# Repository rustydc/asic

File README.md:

# ASIC LLM research prototype

This repository contains the software-model starting point for a fixed-weight
LLM inference appliance built around the Qwen3.5 dense hybrid geometry.

* [`ARCHITECTURE.md`](ARCHITECTURE.md) records the current appliance and pipeline
  decisions, including the balanced FULL-retrieval policy for every global layer.
* [`fixed_llm_poc.py`](fixed_llm_poc.py) is the correctness-oriented PyTorch
  reference model. Its parameter names match the Hugging Face `Qwen3_5` text
  model so released checkpoints load with a prefix rename. It is not an
  optimized long-context training kernel.
* [`fabric/`](fabric/) defines the fixed-weight fabric tile: a via-programmed
  coefficient ROM feeding 64 MAC columns. It holds the bit-exact reference
  model, the coefficient compiler and via-pattern export, the model-to-tile
  mapping with area and latency estimates, synthesizable RTL verified
  against the model with Icarus Verilog, a yosys flow that measures the
  column datapath on open liberty files (sky130, IHP SG13G2, NanGate 45,
  ASAP7), an OpenSTA driver for pre-layout timing, and an OpenROAD
  place-and-route driver with its sky130 and ASAP7 results. `fabric/layer.py`
  and the vector-unit RTL beside the tile are the rest of the layer
  datapath: the norms, the causal convolution, the Gated DeltaNet state
  update and gates, SwiGLU, the residual adds, the rotary embedding and
  the attention core, as a bit-exact fixed-point model with the compiler
  for their constants, checked against the PyTorch reference and against
  the RTL in Icarus. `fabric/memory.py` and its RTL are the memory side:
  the per-context address map, the state DMA, the window and block
  append with the 4-bit index, the index scan and top-K, and the record
  reader into the attention core, with a float twin that reproduces the
  reference retrieval token by token. `fabric/hpi.py` and its RTL are the
  controller for the PSRAM board's chosen device, the AP Memory
  APS512XXN in x16 HPI mode, with a stripe unit over sixteen of them, the
  clock crossing to the core, and the PHY's delay lines with their DLL.
  `fabric/sequencer.py` and its RTL are the token sequencer: a layer's
  dataflow as a program of unit commands, proven against the integer
  layer, scheduled at full size, merged across tokens of different
  contexts so the memory port never waits, and run by a microcoded issue
  engine with per-buffer scoreboards. `fabric/engine.py` and
  `fabric/rtl/fabric_engine.sv` are the layer engine: that controller
  wired to the real tiles, vector units, state engines, attention cores
  and memory port through one vector buffer, running both layers'
  programs bit for bit against the integer model and the memory model,
  over the memory model or the HPI path itself, one token at a time or
  a prefill chunk of tokens on the multi-token tiles.
  `fabric/state.py` is the study that set the recurrent state's format,
  int8 with a per-head scale that carries the decay, halving the traffic
  the schedule showed to dominate; the global layer's traffic followed,
  with a head-major window read in page bursts, a page-per-request index
  scan and int4 keys and values.
* [`clash/`](clash/) contains a synthesizable four-stage ASIC-shard seed with a
  deliberately small fixed-coefficient datapath for early RTL and P&R work.
* [`sim/`](sim/) contains the cycle-stepped 32-stage appliance simulator for
  scheduling, phased global execution, backpressure, link, memory-bandwidth,
  and retrieval-geometry sweep experiments, with an energy model that turns
  the measured energy per MAC into board power at the simulated throughput.
* [`training/`](training/) contains the Qwen3.5 checkpoint importer, the
  retrieval candidates, and a layer-wise activation-distillation harness.
* [`hw/`](hw/) contains the block-level board descriptions of the host-attached
  1U: the 9B board (eight layer ASICs, two head-mode ASICs, sixteen LPDDR5X
  devices, one FPGA on a PCIe cable, a BMC, redundant CRPS supplies) and
  the 27B-class high-end variant (four sixteen-layer ASICs with HBM4 in
  the package, one head ASIC, liquid cooled), their consistency checks
  including a throughput-driven power budget, the rendered block diagrams,
  a derivation of the ASIC package and ball map from the power model and
  the interface list, a generator that turns either description into a
  KiCad 7 project with the board outline and chassis keep-outs, the ring
  placed as a regular polygon of rotated chips, stackup, all nets, and the
  activation ring routed, and a time-domain signal-integrity check of the
  PSRAM clock nets that settled on one clock per device.

## Reference geometries

| Preset | Source model | Hidden | Layers | Body params | Per-ASIC shard |
| --- | --- | ---: | ---: | ---: | ---: |
| `qwen3_5_9b` (default) | Qwen3.5-9B-Base | 4096 | 8 × (3 R + 1 G) | 6.9B | 866M |
| `qwen3_5_4b` | Qwen3.5-4B-Base | 2560 | 8 × (3 R + 1 G) | 3.6B | 447M |
| `qwen3_5_27b` | 27B-class stand-in (Qwen3.5-27B shapes) | 5120 | 16 × (3 R + 1 G) | 22.9B | 1.43B per group, two per die |

Both presets share the same recurrent heads (32 value × 16 key, 128-dim),
attention heads (16 query × 4 KV, 256-dim), and therefore the same per-context
state formats. Only the fabric width differs, so the 4B is a narrow build of the
same design. Select a preset with `ASICLMConfig.from_preset(name)`; every
variant in `training/variants.json` names one.

## Run

Run the tiny model smoke test and the geometry report in an environment with
PyTorch installed:

```bash
python fixed_llm_poc.py
python -m unittest discover -s training/tests -t .
python -m unittest discover -s sim/tests -t .
python -m unittest discover -s fabric/tests -t .   # RTL tests need iverilog; engine tests use verilator if present
python -m unittest discover -s hw/tests -t .
```

Import a released checkpoint (needs the `safetensors` package):

```bash
python -m training.qwen35_import --checkpoint /models/Qwen3.5-9B-Base \
    --output checkpoints/asic_init.pt
```

Simulate both geometries:

```bash
python -m sim.run --config sim/config/baseline.json     # 9B
python -m sim.run --config sim/config/qwen35_4b.json    # 4B
python -m sim.run --config sim/config/qwen35_9b_7nm_hbm.json   # 9B, 7 nm-class die, HBM
python -m sim.run --config sim/config/qwen35_9b_3nm_hbm.json   # 9B, 3 nm-class die, HBM
python -m sim.run --config sim/config/qwen35_27b_2nm_hbm.json  # 27B-class, 2 nm-class die, HBM4 (the high end)
```

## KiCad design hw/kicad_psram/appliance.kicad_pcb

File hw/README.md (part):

# Appliance board (revision A0)

Block-level schematic capture for the first appliance board. `board.yaml` is
the source of truth; `python -m hw.board` checks it and regenerates
`board.svg` (block diagram) and `board.md` (bill of materials, power, pin
budget, ring order). Two variants share the tools: `board_27b.yaml`, the
high-end 27B on HBM, and `board_psram.yaml`, the open-IP 9B on PSRAM
modules. Everything here is a budget to validate, not a vendor-
confirmed number, until the ASIC pinout and power are characterized.

```bash
python -m hw.board            # check, then write board.svg and board.md
python -m unittest discover -s hw/tests -t .
```

## Form factor: a host-attached 1U

The board is a single 420 × 360 mm board in a 1U rack chassis, attached to
a host over a PCIe cable. The first draft was a full-length PCIe card; the
energy model below moved it out of the slot. At 3 pJ per MAC the board
draws 0.5 to 1.6 kW of input across the throughput range, which is a rack
power supply and a row of fans, not a 600 W auxiliary connector on a
passively cooled card. The 1U also has the room the 50K tokens/s package
needs (29 mm bodies on a 230 mm ring) and a management controller. The
chassis layout:

* rear panel: the SlimSAS 8i host connector next to the FPGA, the BMC's
  RJ45, the optional SFP+ cage, the status LEDs;
* rear right: the PSU bay with two CRPS modules in a 1+1 redundant pair;
* the activation ring is a regular polygon in the left two thirds of the
  board, the FPGA at its rear vertex, the shared regulators and the clock
  generator in its middle;
* front: six 40 mm fans blowing front to back across the ring.

## Population

| Part | Qty | Role |
| --- | ---: | --- |
| Layer ASIC | 8 | four decoder layers each, personalized coefficient masks, layer-mode strap |
| Head ASIC | 2 | same die, head-mode strap, each holds half of the 248K-row LM head; no memory |
| LPDDR5X 16 Gb x32 | 16 | two per layer ASIC: 4 GB and 77 GB/s raw per ASIC at 9600 MT/s |
| Controller FPGA | 1 | PCIe Gen4 x8 endpoint over the host cable, ring source and sink, sampling, scheduling |
| DDR4 x16 | 4 | 4 GB on the FPGA for the embedding table and per-context metadata |
| Clock generator | 1 | reference clock to all eleven devices |
| BMC | 1 | AST2600-class: PSU PMBus, fan control, thermal, FPGA console, its own Ethernet |
| Host cable connector | 1 | SlimSAS 8i (SFF-8654): PCIe Gen4 x8 plus sideband to a host adapter card |
| CRPS receptacle | 2 | 12 V from each supply module, 1+1 redundant |
| Fan header | 6 | 4-pin PWM, one per front fan |
| SFP+ cage | 1 (optional) | standalone 10GbE operation, rear panel |

## Topology

One unidirectional activation ring:

```text
FPGA -> A0 -> A1 -> A2 -> A3 -> A4 -> A5 -> A6 -> A7 -> H0 -> H1 -> FPGA
```

Each hop is the 32-bit source-synchronous DDR link from the architecture doc
(36 signals, 2 GB/s raw, under 80 mm). Head chips forward the incoming hidden
vector unchanged and append their top-k logits and partial softmax sum, so no
broadcast path is needed. The FPGA merges the two lists and samples.

On the board the eleven ring nodes sit on the vertices of a regular 11-gon,
clockwise from the FPGA at the rear, each chip rotated so its link-in edge
faces the previous chip and its link-out edge the next. Every hop is then
the same short ribbon. Each layer ASIC's two LPDDR5X devices sit on its
outer edge and its core regulator on its inner edge, rotated with it. All
eleven nodes are on the polygon, heads and FPGA included, because a chip
takes the ring in on one edge and out on the opposite edge: a loop that
dipped into the middle for the heads would have to hairpin back out.

Management is a SPI bus from the FPGA with one chip select per ASIC, a JTAG
chain through all eleven devices, and a fanned-out reference clock. Each ASIC
has a two-pin mode strap (layer or head). The BMC owns the chassis: PSU
PMBus, fan PWM and tach, the core regulators' PMBus, the FPGA's UART
console, and its own Ethernet port.

## Power

ASIC power is no longer a placeholder: it is throughput times energy per
token, from the `power_model` block in `board.yaml`. The one measured input
is the energy of a fixed-weight multiply-accumulate in the column datapath,
0.39 pJ on ASAP7 at the tool's default activity
(`fabric/results/pnr_asap7_signoff.json`), which derates to about 1 pJ for
real activity and projects to 2 to 4 pJ on a 28 nm-class node; the model
carries 3 pJ. Each layer ASIC does 866M MACs per token (9B geometry), each
head ASIC 508M, and the layer ASICs also move about 7.35 MB per token
through their memory at roughly 40 pJ per byte: three 1 MB recurrent-state
read-and-write pairs and the global layer's index scan and selected KV. The other parts keep fixed
budgets (1 W per LPDDR5X, 25 W FPGA, 5 W BMC, 12 W per fan).

At the simulator's corrected 8.2K tokens/s design point that is 27 W per
layer ASIC and 366 W of load, 431 W of 12 V input at 85 percent regulator
efficiency. `board.md` tabulates the same at 5K, 25K and 50K tokens/s: the
board runs from about 330 W to 1.72 kW of input across the throughput range,
and a layer ASIC's core rail goes from 22 A to 184 A at 0.8 V. The supply is
therefore two 2000 W CRPS modules in a 1+1 redundant pair, one of which
carries the whole load, and each ASIC needs a multiphase core regulator.
A 7 nm-class die at about 1 pJ per MAC would put the whole range back under
600 W and make the card viable again; the process choice is the biggest
lever on the power supply and the enclosure.

The power tree is a 12 V intermediate bus from the CRPS modules into
point-of-load regulators. Each ASIC gets its own core buck with PMBus
telemetry so per-chip current is observable during bring-up. The LPDDR5X
rails, 1.8 V I/O, FPGA rails, DDR4 rails, and 3.3 V housekeeping are shared.

## Host interface: PCIe over a cable, and why not Ethernet or PoE

**PoE is out.** The highest PoE class (802.3bt Type 4) delivers 71 W to the
device. This board needs hundreds of watts at any useful throughput. Even a
4B-geometry build at the lowest rate in the table sits well above the PoE
ceiling once the FPGA and memory are counted.

**Ethernet as the data path is viable but not the first build.** The token
traffic is tiny. At 50K tokens/s with a few hundred bytes per token, both
directions together are under 20 MB/s, and a 128K prefill moves 512 KB of
token ids. Even 1GbE would carry it. The reasons to still start with PCIe:

* the FPGA's hard PCIe block is the cheapest working host link, with no
  network stack to write in fabric;
* PCIe round trips are a few microseconds, below the 250 to 500 µs token
  latency target, while a network hop adds tens of microseconds and jitter.

The 1U is host-attached: a SlimSAS 8i cable from the rear panel to a
retimer or host adapter card in the server next to it, the same arrangement
as an external PCIe expansion chassis. PCIe Gen4 x4 is enough bandwidth; the
board wires x8 because the FPGA's hard block is x8 and the cable carries it.

The SFP+ cage on the rear panel keeps the standalone-appliance option open.
The FPGA transceivers are there anyway, so a later firmware can serve a UDP
or gRPC-style token protocol over 10GbE with no board change, and the
chassis already has its own supply and management.

## ASIC package and ball map

`python -m hw.pinout` derives the ASIC package and its ball map from the
board description and writes `hw/pinout/asic_ballmap.csv`, `asic_ballmap.json`
and `report.md`. The pinout is co-designed with the die floorplan and the
substrate, and the substrate is the packaging house's work; what we owe them
is the ball count the power model demands, the package that carries it, and
a ball map with the constraints a substrate and a PCB can both route. The
rules live in the `package_selection` block of `board.yaml`:

* the core rail needs one ball per 0.5 A at the rated throughput, and ground
  matches it plus one return per four signal balls;
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
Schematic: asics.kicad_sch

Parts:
J_SLOT0: slot for U_A0; PCIE_X16_SLOT
J_SLOT1: slot for U_A1; PCIE_X16_SLOT
J_SLOT2: slot for U_A2; PCIE_X16_SLOT
J_SLOT3: slot for U_A3; PCIE_X16_SLOT
J_SLOT4: slot for U_A4; PCIE_X16_SLOT
J_SLOT5: slot for U_A5; PCIE_X16_SLOT
J_SLOT6: slot for U_A6; PCIE_X16_SLOT
J_SLOT7: slot for U_A7; PCIE_X16_SLOT
J_SLOT8: slot for U_H0; PCIE_X16_SLOT
J_SLOT9: slot for U_H1; PCIE_X16_SLOT

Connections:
+12V: J_SLOT0.A1, J_SLOT0.A2, J_SLOT0.A3, J_SLOT0.A4, J_SLOT0.A5, J_SLOT0.A6, J_SLOT0.B1, J_SLOT0.B2, J_SLOT0.B3, J_SLOT0.B4, J_SLOT0.B5, J_SLOT0.B6, J_SLOT1.A1, J_SLOT1.A2, J_SLOT1.A3, J_SLOT1.A4, J_SLOT1.A5, J_SLOT1.A6, J_SLOT1.B1, J_SLOT1.B2, J_SLOT1.B3, J_SLOT1.B4, J_SLOT1.B5, J_SLOT1.B6, J_SLOT2.A1, J_SLOT2.A2, J_SLOT2.A3, J_SLOT2.A4, J_SLOT2.A5, J_SLOT2.A6, J_SLOT2.B1, J_SLOT2.B2, J_SLOT2.B3, J_SLOT2.B4, J_SLOT2.B5, J_SLOT2.B6, J_SLOT3.A1, J_SLOT3.A2, J_SLOT3.A3, J_SLOT3.A4, J_SLOT3.A5, J_SLOT3.A6, J_SLOT3.B1, J_SLOT3.B2, J_SLOT3.B3, J_SLOT3.B4, J_SLOT3.B5, J_SLOT3.B6, J_SLOT4.A1, J_SLOT4.A2, J_SLOT4.A3, J_SLOT4.A4, J_SLOT4.A5, J_SLOT4.A6, J_SLOT4.B1, J_SLOT4.B2, J_SLOT4.B3, J_SLOT4.B4, J_SLOT4.B5, J_SLOT4.B6, J_SLOT5.A1, J_SLOT5.A2, J_SLOT5.A3, J_SLOT5.A4, J_SLOT5.A5, J_SLOT5.A6, J_SLOT5.B1, J_SLOT5.B2, J_SLOT5.B3, J_SLOT5.B4, J_SLOT5.B5, J_SLOT5.B6, J_SLOT6.A1, J_SLOT6.A2, J_SLOT6.A3, J_SLOT6.A4, J_SLOT6.A5, J_SLOT6.A6, J_SLOT6.B1, J_SLOT6.B2, J_SLOT6.B3, J_SLOT6.B4, J_SLOT6.B5, J_SLOT6.B6, J_SLOT7.A1, J_SLOT7.A2, J_SLOT7.A3, J_SLOT7.A4, J_SLOT7.A5, J_SLOT7.A6, J_SLOT7.B1, J_SLOT7.B2, J_SLOT7.B3, J_SLOT7.B4, J_SLOT7.B5, J_SLOT7.B6, J_SLOT8.A1, J_SLOT8.A2, J_SLOT8.A3, J_SLOT8.A4, J_SLOT8.A5, J_SLOT8.A6, J_SLOT8.B1, J_SLOT8.B2, J_SLOT8.B3, J_SLOT8.B4, J_SLOT8.B5, J_SLOT8.B6, J_SLOT9.A1, J_SLOT9.A2, J_SLOT9.A3, J_SLOT9.A4, J_SLOT9.A5, J_SLOT9.A6, J_SLOT9.B1, J_SLOT9.B2, J_SLOT9.B3, J_SLOT9.B4, J_SLOT9.B5, J_SLOT9.B6; also elsewhere on the board
GND: J_SLOT0.A7, J_SLOT0.A8, J_SLOT0.A9, J_SLOT0.A10, J_SLOT0.A11, J_SLOT0.A24, J_SLOT0.A25, J_SLOT0.A26, J_SLOT0.A27, J_SLOT0.A28, J_SLOT0.A29, J_SLOT0.A30, J_SLOT0.A31, J_SLOT0.A32, J_SLOT0.A33, J_SLOT0.A34, J_SLOT0.A35, J_SLOT0.A36, J_SLOT0.A37, J_SLOT0.A38, J_SLOT0.A39, J_SLOT0.A40, J_SLOT0.A41, J_SLOT0.A42, J_SLOT0.A43, J_SLOT0.A44, J_SLOT0.A45, J_SLOT0.A46, J_SLOT0.A47, J_SLOT0.A48, J_SLOT0.A49, J_SLOT0.A64, J_SLOT0.A65, J_SLOT0.A66, J_SLOT0.A67, J_SLOT0.A68, J_SLOT0.A69, J_SLOT0.A70, J_SLOT0.A71, J_SLOT0.A72, J_SLOT0.A73, J_SLOT0.A74, J_SLOT0.A75, J_SLOT0.A76, J_SLOT0.A77, J_SLOT0.A78, J_SLOT0.A79, J_SLOT0.A80, J_SLOT0.A81, J_SLOT0.A82, J_SLOT0.B7, J_SLOT0.B8, J_SLOT0.B9, J_SLOT0.B10, J_SLOT0.B11, J_SLOT0.B24, J_SLOT0.B25, J_SLOT0.B26, J_SLOT0.B27, J_SLOT0.B28, J_SLOT0.B29, J_SLOT0.B30, J_SLOT0.B31, J_SLOT0.B32, J_SLOT0.B33, J_SLOT0.B34, J_SLOT0.B35, J_SLOT0.B36, J_SLOT0.B37, J_SLOT0.B38, J_SLOT0.B39, J_SLOT0.B40, J_SLOT0.B41, J_SLOT0.B42, J_SLOT0.B43, J_SLOT0.B44, J_SLOT0.B45, J_SLOT0.B46, J_SLOT0.B47, J_SLOT0.B48, J_SLOT0.B49, J_SLOT0.B54, J_SLOT0.B55, J_SLOT0.B56, J_SLOT0.B57, J_SLOT0.B58, J_SLOT0.B59, J_SLOT0.B60, J_SLOT0.B61, J_SLOT0.B62, J_SLOT0.B63, J_SLOT0.B64, J_SLOT0.B65, J_SLOT0.B66, J_SLOT0.B67, J_SLOT0.B68, J_SLOT0.B69, J_SLOT0.B70, J_SLOT0.B71, J_SLOT0.B72, J_SLOT0.B73, J_SLOT0.B74, J_SLOT0.B75, J_SLOT0.B76, J_SLOT0.B77, J_SLOT0.B78, J_SLOT0.B79, J_SLOT0.B80, J_SLOT0.B81, J_SLOT0.B82, J_SLOT1.A7, J_SLOT1.A8, J_SLOT1.A9, J_SLOT1.A10, J_SLOT1.A11, J_SLOT1.A24, J_SLOT1.A25, J_SLOT1.A26, J_SLOT1.A27, J_SLOT1.A28, J_SLOT1.A29, J_SLOT1.A30, J_SLOT1.A31, J_SLOT1.A32, J_SLOT1.A33, J_SLOT1.A34, J_SLOT1.A35, J_SLOT1.A36, J_SLOT1.A37, J_SLOT1.A38, J_SLOT1.A39, J_SLOT1.A40, J_SLOT1.A41, J_SLOT1.A42, J_SLOT1.A43, J_SLOT1.A44, J_SLOT1.A45, J_SLOT1.A46, J_SLOT1.A47, J_SLOT1.A48, J_SLOT1.A49, J_SLOT1.A64, J_SLOT1.A65, J_SLOT1.A66, J_SLOT1.A67, J_SLOT1.A68, J_SLOT1.A69, J_SLOT1.A70, J_SLOT1.A71, J_SLOT1.A72, J_SLOT1.A73, J_SLOT1.A74, J_SLOT1.A75, J_SLOT1.A76, J_SLOT1.A77, J_SLOT1.A78, J_SLOT1.A79, J_SLOT1.A80, J_SLOT1.A81, J_SLOT1.A82, J_SLOT1.B7, J_SLOT1.B8, J_SLOT1.B9, J_SLOT1.B10, J_SLOT1.B11, J_SLOT1.B24, J_SLOT1.B25, J_SLOT1.B26, J_SLOT1.B27, J_SLOT1.B28, J_SLOT1.B29, J_SLOT1.B30, J_SLOT1.B31, J_SLOT1.B32, J_SLOT1.B33, J_SLOT1.B34, J_SLOT1.B35, J_SLOT1.B36, J_SLOT1.B37, J_SLOT1.B38, J_SLOT1.B39, J_SLOT1.B40, J_SLOT1.B41, J_SLOT1.B42, J_SLOT1.B43, J_SLOT1.B44, J_SLOT1.B45, J_SLOT1.B46, J_SLOT1.B47, J_SLOT1.B48, J_SLOT1.B49, J_SLOT1.B54, J_SLOT1.B55, J_SLOT1.B56, J_SLOT1.B57, J_SLOT1.B58, J_SLOT1.B59, J_SLOT1.B60, J_SLOT1.B61, J_SLOT1.B62, J_SLOT1.B63, J_SLOT1.B64, J_SLOT1.B65, J_SLOT1.B66, J_SLOT1.B67, J_SLOT1.B68, J_SLOT1.B69, J_SLOT1.B70, J_SLOT1.B71, J_SLOT1.B72, J_SLOT1.B73, J_SLOT1.B74, J_SLOT1.B75, J_SLOT1.B76, J_SLOT1.B77, J_SLOT1.B78, J_SLOT1.B79, J_SLOT1.B80, J_SLOT1.B81, J_SLOT1.B82, J_SLOT2.A7, J_SLOT2.A8, J_SLOT2.A9, J_SLOT2.A10, J_SLOT2.A11, J_SLOT2.A24, J_SLOT2.A25, J_SLOT2.A26, J_SLOT2.A27, J_SLOT2.A28, J_SLOT2.A29, J_SLOT2.A30, J_SLOT2.A31, J_SLOT2.A32, J_SLOT2.A33, J_SLOT2.A34, J_SLOT2.A35, J_SLOT2.A36, J_SLOT2.A37, J_SLOT2.A38, J_SLOT2.A39, J_SLOT2.A40, J_SLOT2.A41, J_SLOT2.A42, J_SLOT2.A43, J_SLOT2.A44, J_SLOT2.A45, J_SLOT2.A46, J_SLOT2.A47, J_SLOT2.A48, J_SLOT2.A49, J_SLOT2.A64, J_SLOT2.A65, J_SLOT2.A66, J_SLOT2.A67, J_SLOT2.A68, J_SLOT2.A69, J_SLOT2.A70, J_SLOT2.A71, J_SLOT2.A72, J_SLOT2.A73, J_SLOT2.A74, J_SLOT2.A75, J_SLOT2.A76, J_SLOT2.A77, J_SLOT2.A78, J_SLOT2.A79, J_SLOT2.A80, J_SLOT2.A81, J_SLOT2.A82, J_SLOT2.B7, J_SLOT2.B8, J_SLOT2.B9, J_SLOT2.B10, J_SLOT2.B11, J_SLOT2.B24, J_SLOT2.B25, J_SLOT2.B26, J_SLOT2.B27, J_SLOT2.B28, J_SLOT2.B29, J_SLOT2.B30, J_SLOT2.B31, J_SLOT2.B32, J_SLOT2.B33, J_SLOT2.B34, J_SLOT2.B35, J_SLOT2.B36, J_SLOT2.B37, J_SLOT2.B38, J_SLOT2.B39, J_SLOT2.B40, J_SLOT2.B41, J_SLOT2.B42, J_SLOT2.B43, J_SLOT2.B44, J_SLOT2.B45, J_SLOT2.B46, J_SLOT2.B47, J_SLOT2.B48, J_SLOT2.B49, J_SLOT2.B54, J_SLOT2.B55, J_SLOT2.B56, J_SLOT2.B57, J_SLOT2.B58, J_SLOT2.B59, J_SLOT2.B60, J_SLOT2.B61, J_SLOT2.B62, J_SLOT2.B63, J_SLOT2.B64, J_SLOT2.B65, J_SLOT2.B66, J_SLOT2.B67, J_SLOT2.B68, J_SLOT2.B69, J_SLOT2.B70, J_SLOT2.B71, J_SLOT2.B72, J_SLOT2.B73, J_SLOT2.B74, J_SLOT2.B75, J_SLOT2.B76, J_SLOT2.B77, J_SLOT2.B78, J_SLOT2.B79, J_SLOT2.B80, J_SLOT2.B81, J_SLOT2.B82, J_SLOT3.A7, J_SLOT3.A8, J_SLOT3.A9, J_SLOT3.A10, J_SLOT3.A11, J_SLOT3.A24, J_SLOT3.A25, J_SLOT3.A26, J_SLOT3.A27, J_SLOT3.A28, J_SLOT3.A29, J_SLOT3.A30, J_SLOT3.A31, J_SLOT3.A32, J_SLOT3.A33, J_SLOT3.A34, J_SLOT3.A35, J_SLOT3.A36, J_SLOT3.A37, J_SLOT3.A38, J_SLOT3.A39, J_SLOT3.A40, J_SLOT3.A41, J_SLOT3.A42, J_SLOT3.A43, J_SLOT3.A44, J_SLOT3.A45, J_SLOT3.A46, J_SLOT3.A47, J_SLOT3.A48, J_SLOT3.A49, J_SLOT3.A64, J_SLOT3.A65, J_SLOT3.A66, J_SLOT3.A67, J_SLOT3.A68, J_SLOT3.A69, J_SLOT3.A70, J_SLOT3.A71, J_SLOT3.A72, J_SLOT3.A73, J_SLOT3.A74, J_SLOT3.A75, J_SLOT3.A76, J_SLOT3.A77, J_SLOT3.A78, J_SLOT3.A79, J_SLOT3.A80, J_SLOT3.A81, J_SLOT3.A82, J_SLOT3.B7, J_SLOT3.B8, J_SLOT3.B9, J_SLOT3.B10, J_SLOT3.B11, J_SLOT3.B24, J_SLOT3.B25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; also elsewhere on the board
JTAG_TCK: J_SLOT0.A55, J_SLOT1.A55, J_SLOT2.A55, J_SLOT3.A55, J_SLOT4.A55, J_SLOT5.A55, J_SLOT6.A55, J_SLOT7.A55, J_SLOT8.A55, J_SLOT9.A55; also elsewhere on the board
JTAG_TDO_A0: J_SLOT0.A58, J_SLOT1.A57
JTAG_TDO_A1: J_SLOT1.A58, J_SLOT2.A57
JTAG_TDO_A2: J_SLOT2.A58, J_SLOT3.A57
JTAG_TDO_A3: J_SLOT3.A58, J_SLOT4.A57
JTAG_TDO_A4: J_SLOT4.A58, J_SLOT5.A57
JTAG_TDO_A5: J_SLOT5.A58, J_SLOT6.A57
JTAG_TDO_A6: J_SLOT6.A58, J_SLOT7.A57
JTAG_TDO_A7: J_SLOT7.A58, J_SLOT8.A57
JTAG_TDO_FPGA: J_SLOT0.A57; also elsewhere on the board
JTAG_TDO_H0: J_SLOT8.A58, J_SLOT9.A57
JTAG_TDO_H1: J_SLOT9.A58
JTAG_TMS: J_SLOT0.A56, J_SLOT1.A56, J_SLOT2.A56, J_SLOT3.A56, J_SLOT4.A56, J_SLOT5.A56, J_SLOT6.A56, J_SLOT7.A56, J_SLOT8.A56, J_SLOT9.A56; also elsewhere on the board
JTAG_TRST: J_SLOT0.A59, J_SLOT1.A59, J_SLOT2.A59, J_SLOT3.A59, J_SLOT4.A59, J_SLOT5.A59, J_SLOT6.A59, J_SLOT7.A59, J_SLOT8.A59, J_SLOT9.A59; also elsewhere on the board
LINK0_CLOCK: J_SLOT0.A20; also elsewhere on the board
LINK0_DATA0: J_SLOT0.A12; also elsewhere on the board
LINK0_DATA1: J_SLOT0.A13; also elsewhere on the board
LINK0_DATA2: J_SLOT0.A14; also elsewhere on the board
LINK0_DATA3: J_SLOT0.A15; also elsewhere on the board
LINK0_DATA4: J_SLOT0.A16; also elsewhere on the board
LINK0_DATA5: J_SLOT0.A17; also elsewhere on the board
LINK0_DATA6: J_SLOT0.A18; also elsewhere on the board
LINK0_DATA7: J_SLOT0.A19; also elsewhere on the board
LINK0_READY_BACK: J_SLOT0.A22; also elsewhere on the board
LINK0_SOF: J_SLOT0.A23; also elsewhere on the board
LINK0_VALID: J_SLOT0.A21; also elsewhere on the board
LINK1_CLOCK: J_SLOT0.B20, J_SLOT1.A20
LINK1_DATA0: J_SLOT0.B12, J_SLOT1.A12
LINK1_DATA1: J_SLOT0.B13, J_SLOT1.A13
LINK1_DATA2: J_SLOT0.B14, J_SLOT1.A14
LINK1_DATA3: J_SLOT0.B15, J_SLOT1.A15
LINK1_DATA4: J_SLOT0.B16, J_SLOT1.A16
LINK1_DATA5: J_SLOT0.B17, J_SLOT1.A17
LINK1_DATA6: J_SLOT0.B18, J_SLOT1.A18
LINK1_DATA7: J_SLOT0.B19, J_SLOT1.A19
LINK1_READY_BACK: J_SLOT0.B22, J_SLOT1.A22
LINK1_SOF: J_SLOT0.B23, J_SLOT1.A23
LINK1_VALID: J_SLOT0.B21, J_SLOT1.A21
LINK2_CLOCK: J_SLOT1.B20, J_SLOT2.A20
LINK2_DATA0: J_SLOT1.B12, J_SLOT2.A12
LINK2_DATA1: J_SLOT1.B13, J_SLOT2.A13
LINK2_DATA2: J_SLOT1.B14, J_SLOT2.A14
LINK2_DATA3: J_SLOT1.B15, J_SLOT2.A15
LINK2_DATA4: J_SLOT1.B16, J_SLOT2.A16
LINK2_DATA5: J_SLOT1.B17, J_SLOT2.A17
LINK2_DATA6: J_SLOT1.B18, J_SLOT2.A18
LINK2_DATA7: J_SLOT1.B19, J_SLOT2.A19
LINK2_READY_BACK: J_SLOT1.B22, J_SLOT2.A22
LINK2_SOF: J_SLOT1.B23, J_SLOT2.A23
LINK2_VALID: J_SLOT1.B21, J_SLOT2.A21
LINK3_CLOCK: J_SLOT2.B20, J_SLOT3.A20
LINK3_DATA0: J_SLOT2.B12, J_SLOT3.A12
LINK3_DATA1: J_SLOT2.B13, J_SLOT3.A13
LINK3_DATA2: J_SLOT2.B14, J_SLOT3.A14
LINK3_DATA3: J_SLOT2.B15, J_SLOT3.A15
LINK3_DATA4: J_SLOT2.B16, J_SLOT3.A16
LINK3_DATA5: J_SLOT2.B17, J_SLOT3.A17
LINK3_DATA6: J_SLOT2.B18, J_SLOT3.A18
LINK3_DATA7: J_SLOT2.B19, J_SLOT3.A19
LINK3_READY_BACK: J_SLOT2.B22, J_SLOT3.A22
LINK3_SOF: J_SLOT2.B23, J_SLOT3.A23
LINK3_VALID: J_SLOT2.B21, J_SLOT3.A21
LINK4_CLOCK: J_SLOT3.B20, J_SLOT4.A20
LINK4_DATA0: J_SLOT3.B12, J_SLOT4.A12
LINK4_DATA1: J_SLOT3.B13, J_SLOT4.A13
LINK4_DATA2: J_SLOT3.B14, J_SLOT4.A14
LINK4_DATA3: J_SLOT3.B15, J_SLOT4.A15
LINK4_DATA4: J_SLOT3.B16, J_SLOT4.A16
LINK4_DATA5: J_SLOT3.B17, J_SLOT4.A17
LINK4_DATA6: J_SLOT3.B18, J_SLOT4.A18
LINK4_DATA7: J_SLOT3.B19, J_SLOT4.A19
LINK4_READY_BACK: J_SLOT3.B22, J_SLOT4.A22
LINK4_SOF: J_SLOT3.B23, J_SLOT4.A23
LINK4_VALID: J_SLOT3.B21, J_SLOT4.A21
LINK5_CLOCK: J_SLOT4.B20, J_SLOT5.A20
LINK5_DATA0: J_SLOT4.B12, J_SLOT5.A12
LINK5_DATA1: J_SLOT4.B13, J_SLOT5.A13
LINK5_DATA2: J_SLOT4.B14, J_SLOT5.A14
LINK5_DATA3: J_SLOT4.B15, J_SLOT5.A15
LINK5_DATA4: J_SLOT4.B16, J_SLOT5.A16
LINK5_DATA5: J_SLOT4.B17, J_SLOT5.A17
LINK5_DATA6: J_SLOT4.B18, J_SLOT5.A18
LINK5_DATA7: J_SLOT4.B19, J_SLOT5.A19
LINK5_READY_BACK: J_SLOT4.B22, J_SLOT5.A22
LINK5_SOF: J_SLOT4.B23, J_SLOT5.A23
LINK5_VALID: J_SLOT4.B21, J_SLOT5.A21
LINK6_CLOCK: J_SLOT5.B20, J_SLOT6.A20
LINK6_DATA0: J_SLOT5.B12, J_SLOT6.A12
LINK6_DATA1: J_SLOT5.B13, J_SLOT6.A13
LINK6_DATA2: J_SLOT5.B14, J_SLOT6.A14
LINK6_DATA3: J_SLOT5.B15, J_SLOT6.A15
LINK6_DATA4: J_SLOT5.B16, J_SLOT6.A16
LINK6_DATA5: J_SLOT5.B17, J_SLOT6.A17
LINK6_DATA6: J_SLOT5.B18, J_SLOT6.A18
LINK6_DATA7: J_SLOT5.B19, J_SLOT6.A19
LINK6_READY_BACK: J_SLOT5.B22, J_SLOT6.A22
LINK6_SOF: J_SLOT5.B23, J_SLOT6.A23
LINK6_VALID: J_SLOT5.B21, J_SLOT6.A21
LINK7_CLOCK: J_SLOT6.B20, J_SLOT7.A20
LINK7_DATA0: J_SLOT6.B12, J_SLOT7.A12
LINK7_DATA1: J_SLOT6.B13, J_SLOT7.A13
LINK7_DATA2: J_SLOT6.B14, J_SLOT7.A14
LINK7_DATA3: J_SLOT6.B15, J_SLOT7.A15
LINK7_DATA4: J_SLOT6.B16, J_SLOT7.A16
LINK7_DATA5: J_SLOT6.B17, J_SLOT7.A17
LINK7_DATA6: J_SLOT6.B18, J_SLOT7.A18
LINK7_DATA7: J_SLOT6.B19, J_SLOT7.A19
LINK7_READY_BACK: J_SLOT6.B22, J_SLOT7.A22
LINK7_SOF: J_SLOT6.B23, J_SLOT7.A23
LINK7_VALID: J_SLOT6.B21, J_SLOT7.A21
LINK8_CLOCK: J_SLOT7.B20, J_SLOT8.A20
LINK8_DATA0: J_SLOT7.B12, J_SLOT8.A12
LINK8_DATA1: J_SLOT7.B13, J_SLOT8.A13
LINK8_DATA2: J_SLOT7.B14, J_SLOT8.A14
LINK8_DATA3: J_SLOT7.B15, J_SLOT8.A15
LINK8_DATA4: J_SLOT7.B16, J_SLOT8.A16
LINK8_DATA5: J_SLOT7.B17, J_SLOT8.A17
LINK8_DATA6: J_SLOT7.B18, J_SLOT8.A18
LINK8_DATA7: J_SLOT7.B19, J_SLOT8.A19
LINK8_READY_BACK: J_SLOT7.B22, J_SLOT8.A22
LINK8_SOF: J_SLOT7.B23, J_SLOT8.A23
LINK8_VALID: J_SLOT7.B21, J_SLOT8.A21
LINK9_CLOCK: J_SLOT8.B20, J_SLOT9.A20
LINK9_DATA0: J_SLOT8.B12, J_SLOT9.A12
LINK9_DATA1: J_SLOT8.B13, J_SLOT9.A13
LINK9_DATA2: J_SLOT8.B14, J_SLOT9.A14
LINK9_DATA3: J_SLOT8.B15, J_SLOT9.A15
LINK9_DATA4: J_SLOT8.B16, J_SLOT9.A16
LINK9_DATA5: J_SLOT8.B17, J_SLOT9.A17
LINK9_DATA6: J_SLOT8.B18, J_SLOT9.A18
LINK9_DATA7: J_SLOT8.B19, J_SLOT9.A19
LINK9_READY_BACK: J_SLOT8.B22, J_SLOT9.A22
LINK9_SOF: J_SLOT8.B23, J_SLOT9.A23
LINK9_VALID: J_SLOT8.B21, J_SLOT9.A21
LINK10_CLOCK: J_SLOT9.B20; also elsewhere on the board
LINK10_DATA0: J_SLOT9.B12; also elsewhere on the board
LINK10_DATA1: J_SLOT9.B13; also elsewhere on the board
LINK10_DATA2: J_SLOT9.B14; also elsewhere on the board
LINK10_DATA3: J_SLOT9.B15; also elsewhere on the board
LINK10_DATA4: J_SLOT9.B16; also elsewhere on the board
LINK10_DATA5: J_SLOT9.B17; also elsewhere on the board
LINK10_DATA6: J_SLOT9.B18; also elsewhere on the board
LINK10_DATA7: J_SLOT9.B19; also elsewhere on the board
LINK10_READY_BACK: J_SLOT9.B22; also elsewhere on the board
LINK10_SOF: J_SLOT9.B23; also elsewhere on the board
LINK10_VALID: J_SLOT9.B21; also elsewhere on the board
MGMT_CS_A0: J_SLOT0.A53; also elsewhere on the board
MGMT_CS_A1: J_SLOT1.A53; also elsewhere on the board
MGMT_CS_A2: J_SLOT2.A53; also elsewhere on the board
MGMT_CS_A3: J_SLOT3.A53; also elsewhere on the board
MGMT_CS_A4: J_SLOT4.A53; also elsewhere on the board
MGMT_CS_A5: J_SLOT5.A53; also elsewhere on the board
MGMT_CS_A6: J_SLOT6.A53; also elsewhere on the board
MGMT_CS_A7: J_SLOT7.A53; also elsewhere on the board
MGMT_CS_H0: J_SLOT8.A53; also elsewhere on the board
MGMT_CS_H1: J_SLOT9.A53; also elsewhere on the board
MGMT_IRQ_A0: J_SLOT0.A54; also elsewhere on the board
MGMT_IRQ_A1: J_SLOT1.A54; also elsewhere on the board
MGMT_IRQ_A2: J_SLOT2.A54; also elsewhere on the board
MGMT_IRQ_A3: J_SLOT3.A54; also elsewhere on the board
MGMT_IRQ_A4: J_SLOT4.A54; also elsewhere on the board
MGMT_IRQ_A5: J_SLOT5.A54; also elsewhere on the board
MGMT_IRQ_A6: J_SLOT6.A54; also elsewhere on the board
MGMT_IRQ_A7: J_SLOT7.A54; also elsewhere on the board
MGMT_IRQ_H0: J_SLOT8.A54; also elsewhere on the board
MGMT_IRQ_H1: J_SLOT9.A54; also elsewhere on the board
MGMT_MISO: J_SLOT0.A52, J_SLOT1.A52, J_SLOT2.A52, J_SLOT3.A52, J_SLOT4.A52, J_SLOT5.A52, J_SLOT6.A52, J_SLOT7.A52, J_SLOT8.A52, J_SLOT9.A52; also elsewhere on the board
MGMT_MOSI: J_SLOT0.A51, J_SLOT1.A51, J_SLOT2.A51, J_SLOT3.A51, J_SLOT4.A51, J_SLOT5.A51, J_SLOT6.A51, J_SLOT7.A51, J_SLOT8.A51, J_SLOT9.A51; also elsewhere on the board
MGMT_SCLK: J_SLOT0.A50, J_SLOT1.A50, J_SLOT2.A50, J_SLOT3.A50, J_SLOT4.A50, J_SLOT5.A50, J_SLOT6.A50, J_SLOT7.A50, J_SLOT8.A50, J_SLOT9.A50; also elsewhere on the board
MODE0_A0: J_SLOT0.A62
MODE0_A1: J_SLOT1.A62
MODE0_A2: J_SLOT2.A62
MODE0_A3: J_SLOT3.A62
MODE0_A4: J_SLOT4.A62
MODE0_A5: J_SLOT5.A62
MODE0_A6: J_SLOT6.A62
MODE0_A7: J_SLOT7.A62
MODE0_H0: J_SLOT8.A62
MODE0_H1: J_SLOT9.A62
MODE1_A0: J_SLOT0.A63
MODE1_A1: J_SLOT1.A63
MODE1_A2: J_SLOT2.A63
MODE1_A3: J_SLOT3.A63
MODE1_A4: J_SLOT4.A63
MODE1_A5: J_SLOT5.A63
MODE1_A6: J_SLOT6.A63
MODE1_A7: J_SLOT7.A63
MODE1_H0: J_SLOT8.A63
MODE1_H1: J_SLOT9.A63
PMB_SCL: J_SLOT0.B50, J_SLOT1.B50, J_SLOT2.B50, J_SLOT3.B50, J_SLOT4.B50, J_SLOT5.B50, J_SLOT6.B50, J_SLOT7.B50, J_SLOT8.B50, J_SLOT9.B50; also elsewhere on the board
PMB_SDA: J_SLOT0.B51, J_SLOT1.B51, J_SLOT2.B51, J_SLOT3.B51, J_SLOT4.B51, J_SLOT5.B51, J_SLOT6.B51, J_SLOT7.B51, J_SLOT8.B51, J_SLOT9.B51; also elsewhere on the board
PRSNT_A0: J_SLOT0.B53
PRSNT_A1: J_SLOT1.B53
PRSNT_A2: J_SLOT2.B53
PRSNT_A3: J_SLOT3.B53
PRSNT_A4: J_SLOT4.B53
PRSNT_A5: J_SLOT5.B53
PRSNT_A6: J_SLOT6.B53
PRSNT_A7: J_SLOT7.B53
PRSNT_H0: J_SLOT8.B53
PRSNT_H1: J_SLOT9.B53
REFCLK_A0_N: J_SLOT0.A61; also elsewhere on the board
REFCLK_A0_P: J_SLOT0.A60; also elsewhere on the board
REFCLK_A1_N: J_SLOT1.A61; also elsewhere on the board
REFCLK_A1_P: J_SLOT1.A60; also elsewhere on the board
REFCLK_A2_N: J_SLOT2.A61; also elsewhere on the board
REFCLK_A2_P: J_SLOT2.A60; also elsewhere on the board
REFCLK_A3_N: J_SLOT3.A61; also elsewhere on the board
REFCLK_A3_P: J_SLOT3.A60; also elsewhere on the board
REFCLK_A4_N: J_SLOT4.A61; also elsewhere on the board
REFCLK_A4_P: J_SLOT4.A60; also elsewhere on the board
REFCLK_A5_N: J_SLOT5.A61; also elsewhere on the board
REFCLK_A5_P: J_SLOT5.A60; also elsewhere on the board
REFCLK_A6_N: J_SLOT6.A61; also elsewhere on the board
REFCLK_A6_P: J_SLOT6.A60; also elsewhere on the board
REFCLK_A7_N: J_SLOT7.A61; also elsewhere on the board
REFCLK_A7_P: J_SLOT7.A60; also elsewhere on the board
REFCLK_H0_N: J_SLOT8.A61; also elsewhere on the board
REFCLK_H0_P: J_SLOT8.A60; also elsewhere on the board
REFCLK_H1_N: J_SLOT9.A61; also elsewhere on the board
REFCLK_H1_P: J_SLOT9.A60; also elsewhere on the board
VRM_EN_A0: J_SLOT0.B52
VRM_EN_A1: J_SLOT1.B52
VRM_EN_A2: J_SLOT2.B52
VRM_EN_A3: J_SLOT3.B52
VRM_EN_A4: J_SLOT4.B52
VRM_EN_A5: J_SLOT5.B52
VRM_EN_A6: J_SLOT6.B52
VRM_EN_A7: J_SLOT7.B52
VRM_EN_H0: J_SLOT8.B52
VRM_EN_H1: J_SLOT9.B52

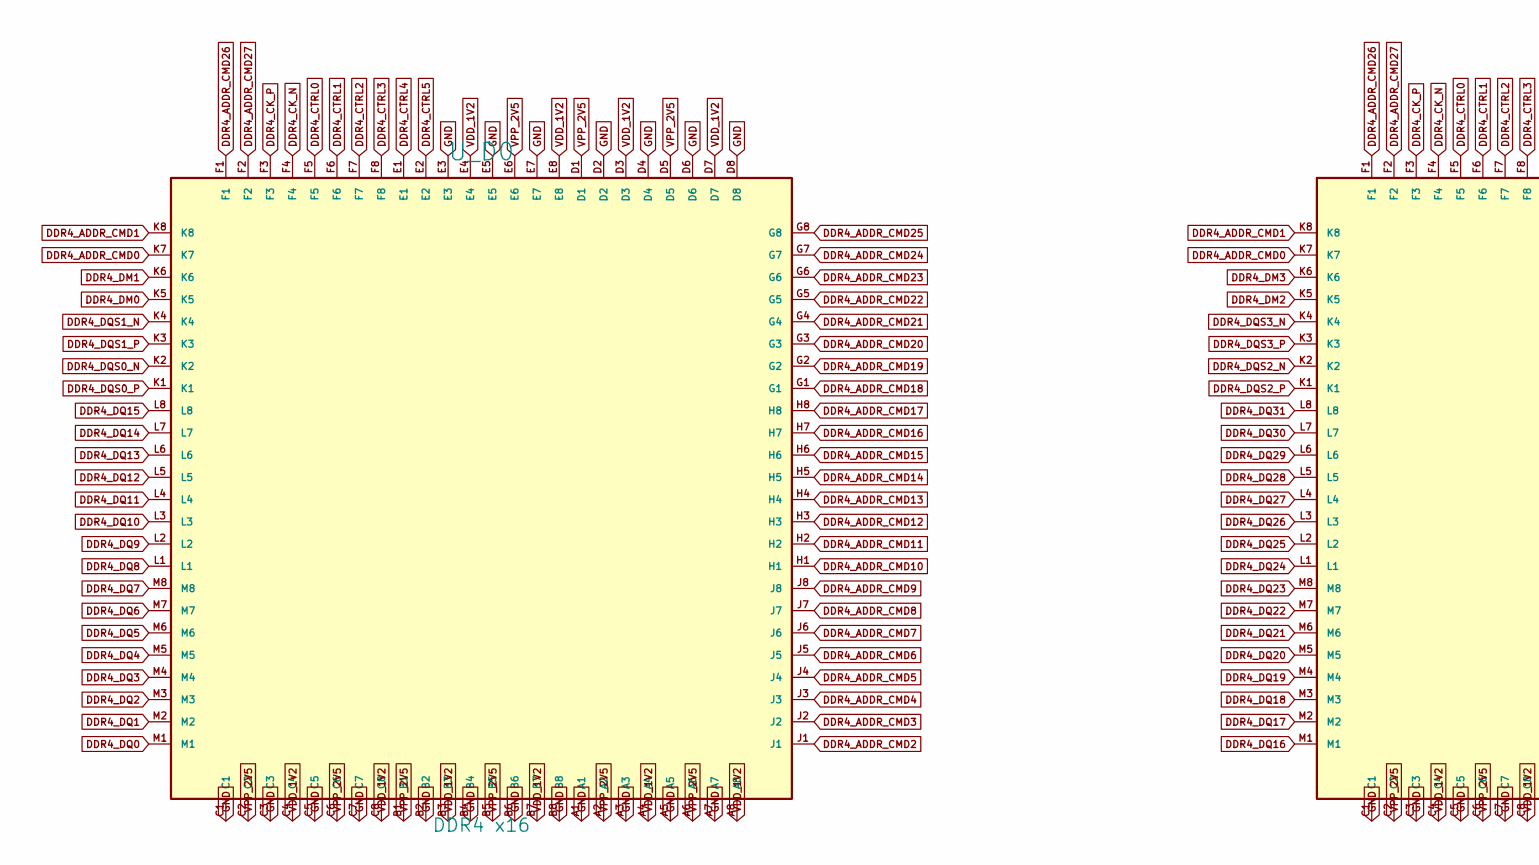
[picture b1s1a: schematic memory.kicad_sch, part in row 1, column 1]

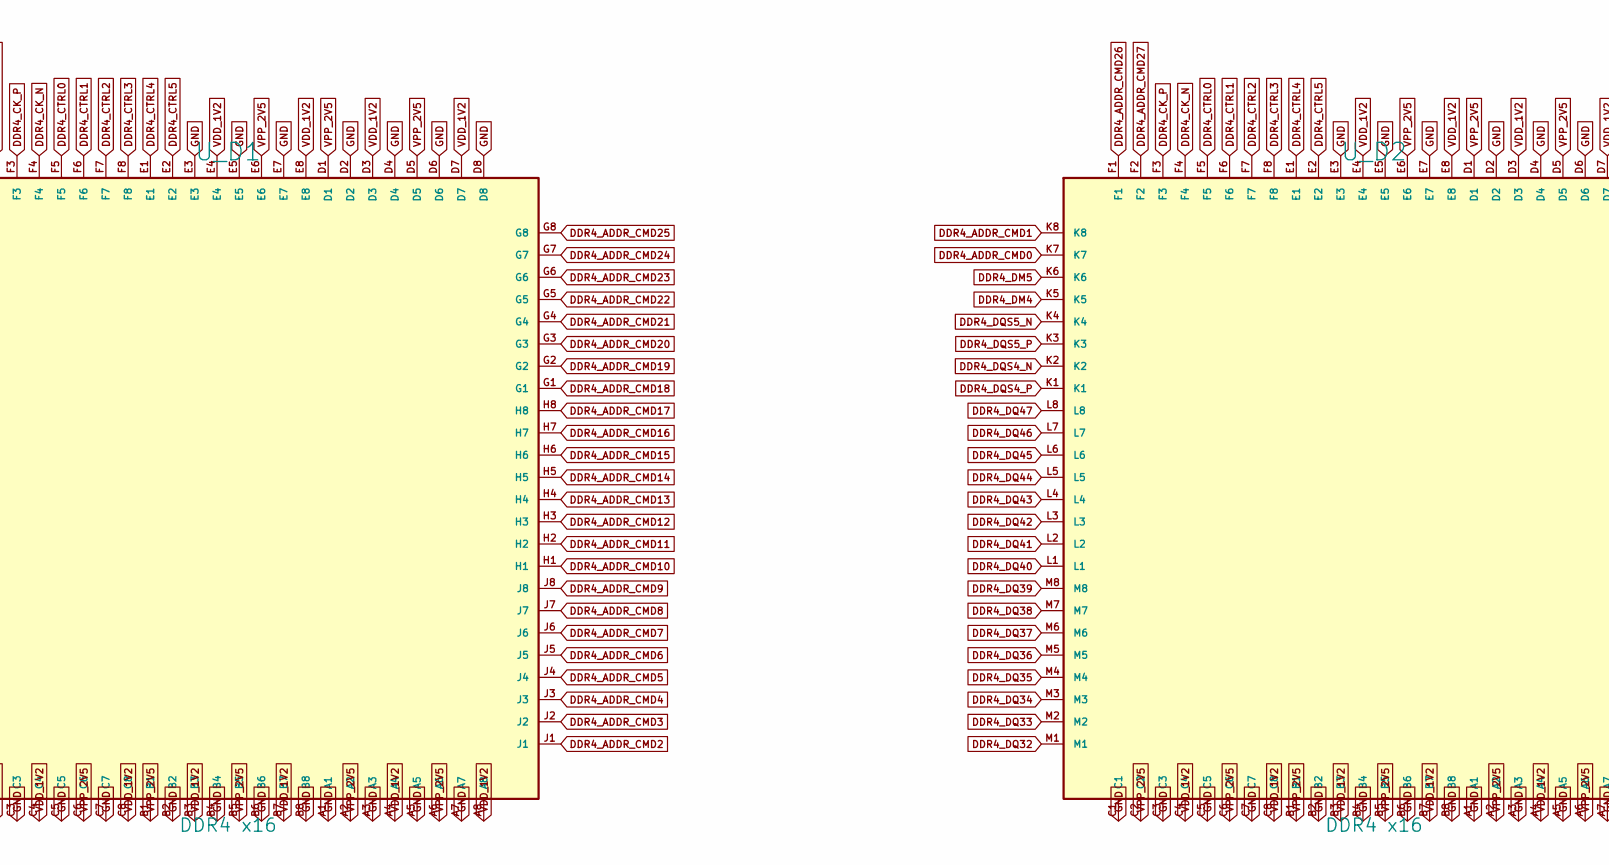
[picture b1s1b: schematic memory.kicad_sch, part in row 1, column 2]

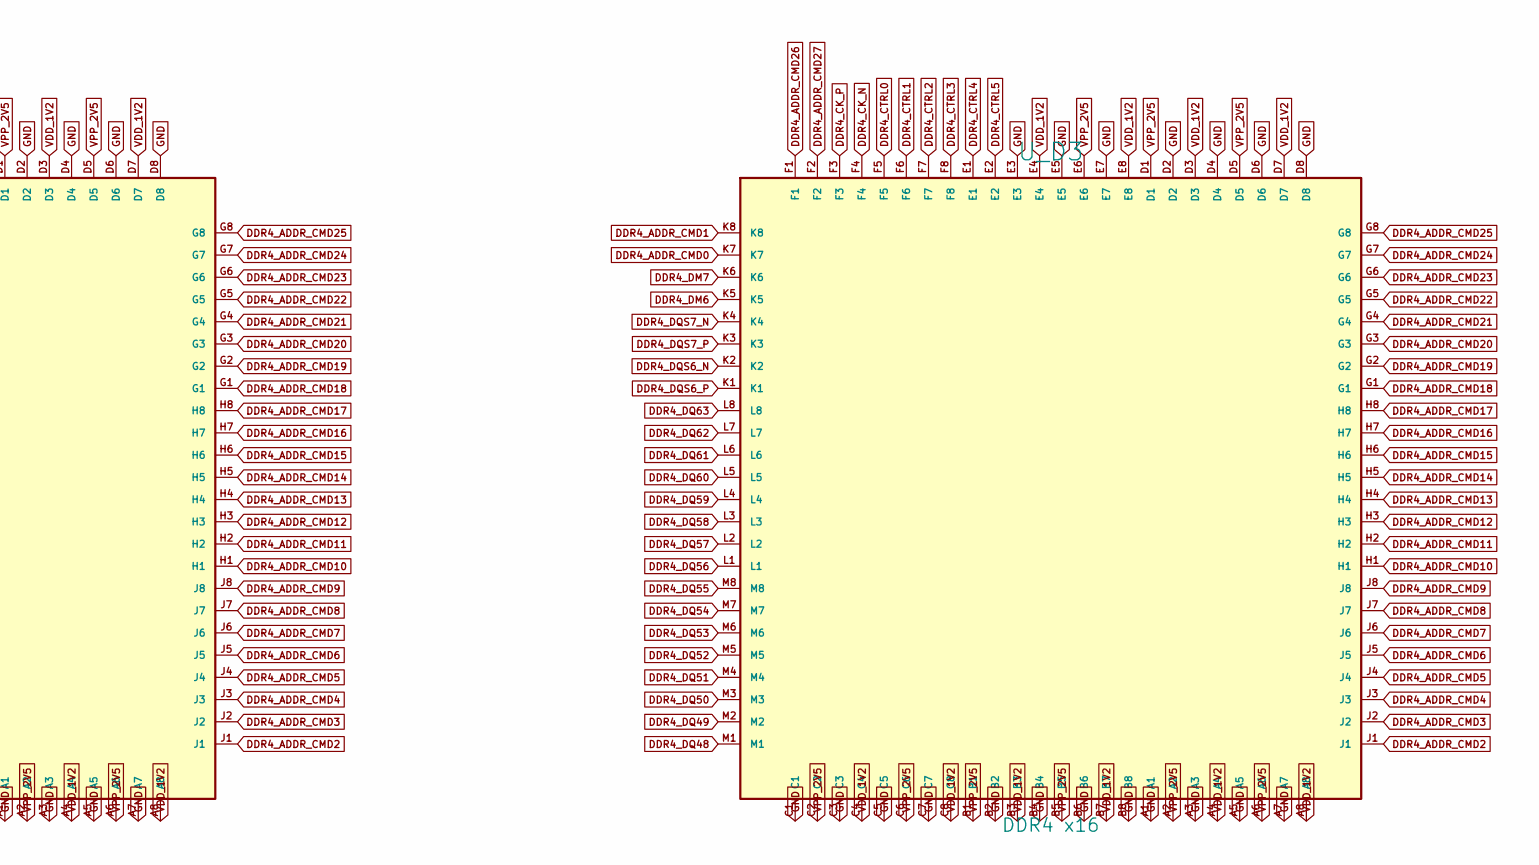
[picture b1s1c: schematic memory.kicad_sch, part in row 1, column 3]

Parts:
U_D0, U_D1, U_D2, U_D3: DDR4 x16; FBGA96_8x12_P0.8

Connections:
DDR4_ADDR_CMD0: U_D0.K7, U_D1.K7, U_D2.K7, U_D3.K7; also elsewhere on the board
DDR4_ADDR_CMD1: U_D0.K8, U_D1.K8, U_D2.K8, U_D3.K8; also elsewhere on the board
DDR4_ADDR_CMD2: U_D0.J1, U_D1.J1, U_D2.J1, U_D3.J1; also elsewhere on the board
DDR4_ADDR_CMD3: U_D0.J2, U_D1.J2, U_D2.J2, U_D3.J2; also elsewhere on the board
DDR4_ADDR_CMD4: U_D0.J3, U_D1.J3, U_D2.J3, U_D3.J3; also elsewhere on the board
DDR4_ADDR_CMD5: U_D0.J4, U_D1.J4, U_D2.J4, U_D3.J4; also elsewhere on the board
DDR4_ADDR_CMD6: U_D0.J5, U_D1.J5, U_D2.J5, U_D3.J5; also elsewhere on the board
DDR4_ADDR_CMD7: U_D0.J6, U_D1.J6, U_D2.J6, U_D3.J6; also elsewhere on the board
DDR4_ADDR_CMD8: U_D0.J7, U_D1.J7, U_D2.J7, U_D3.J7; also elsewhere on the board
DDR4_ADDR_CMD9: U_D0.J8, U_D1.J8, U_D2.J8, U_D3.J8; also elsewhere on the board
DDR4_ADDR_CMD10: U_D0.H1, U_D1.H1, U_D2.H1, U_D3.H1; also elsewhere on the board
DDR4_ADDR_CMD11: U_D0.H2, U_D1.H2, U_D2.H2, U_D3.H2; also elsewhere on the board
DDR4_ADDR_CMD12: U_D0.H3, U_D1.H3, U_D2.H3, U_D3.H3; also elsewhere on the board
DDR4_ADDR_CMD13: U_D0.H4, U_D1.H4, U_D2.H4, U_D3.H4; also elsewhere on the board
DDR4_ADDR_CMD14: U_D0.H5, U_D1.H5, U_D2.H5, U_D3.H5; also elsewhere on the board
DDR4_ADDR_CMD15: U_D0.H6, U_D1.H6, U_D2.H6, U_D3.H6; also elsewhere on the board
DDR4_ADDR_CMD16: U_D0.H7, U_D1.H7, U_D2.H7, U_D3.H7; also elsewhere on the board
DDR4_ADDR_CMD17: U_D0.H8, U_D1.H8, U_D2.H8, U_D3.H8; also elsewhere on the board
DDR4_ADDR_CMD18: U_D0.G1, U_D1.G1, U_D2.G1, U_D3.G1; also elsewhere on the board
DDR4_ADDR_CMD19: U_D0.G2, U_D1.G2, U_D2.G2, U_D3.G2; also elsewhere on the board
DDR4_ADDR_CMD20: U_D0.G3, U_D1.G3, U_D2.G3, U_D3.G3; also elsewhere on the board
DDR4_ADDR_CMD21: U_D0.G4, U_D1.G4, U_D2.G4, U_D3.G4; also elsewhere on the board
DDR4_ADDR_CMD22: U_D0.G5, U_D1.G5, U_D2.G5, U_D3.G5; also elsewhere on the board
DDR4_ADDR_CMD23: U_D0.G6, U_D1.G6, U_D2.G6, U_D3.G6; also elsewhere on the board
DDR4_ADDR_CMD24: U_D0.G7, U_D1.G7, U_D2.G7, U_D3.G7; also elsewhere on the board
DDR4_ADDR_CMD25: U_D0.G8, U_D1.G8, U_D2.G8, U_D3.G8; also elsewhere on the board
DDR4_ADDR_CMD26: U_D0.F1, U_D1.F1, U_D2.F1, U_D3.F1; also elsewhere on the board
DDR4_ADDR_CMD27: U_D0.F2, U_D1.F2, U_D2.F2, U_D3.F2; also elsewhere on the board
DDR4_CK_N: U_D0.F4, U_D1.F4, U_D2.F4, U_D3.F4; also elsewhere on the board
DDR4_CK_P: U_D0.F3, U_D1.F3, U_D2.F3, U_D3.F3; also elsewhere on the board
DDR4_CTRL0: U_D0.F5, U_D1.F5, U_D2.F5, U_D3.F5; also elsewhere on the board
DDR4_CTRL1: U_D0.F6, U_D1.F6, U_D2.F6, U_D3.F6; also elsewhere on the board
DDR4_CTRL2: U_D0.F7, U_D1.F7, U_D2.F7, U_D3.F7; also elsewhere on the board
DDR4_CTRL3: U_D0.F8, U_D1.F8, U_D2.F8, U_D3.F8; also elsewhere on the board
DDR4_CTRL4: U_D0.E1, U_D1.E1, U_D2.E1, U_D3.E1; also elsewhere on the board
DDR4_CTRL5: U_D0.E2, U_D1.E2, U_D2.E2, U_D3.E2; also elsewhere on the board
DDR4_DM0: U_D0.K5; also elsewhere on the board
DDR4_DM1: U_D0.K6; also elsewhere on the board
DDR4_DM2: U_D1.K5; also elsewhere on the board
DDR4_DM3: U_D1.K6; also elsewhere on the board
DDR4_DM4: U_D2.K5; also elsewhere on the board
DDR4_DM5: U_D2.K6; also elsewhere on the board
DDR4_DM6: U_D3.K5; also elsewhere on the board
DDR4_DM7: U_D3.K6; also elsewhere on the board
DDR4_DQ0: U_D0.M1; also elsewhere on the board
DDR4_DQ1: U_D0.M2; also elsewhere on the board
DDR4_DQ2: U_D0.M3; also elsewhere on the board
DDR4_DQ3: U_D0.M4; also elsewhere on the board
DDR4_DQ4: U_D0.M5; also elsewhere on the board
DDR4_DQ5: U_D0.M6; also elsewhere on the board
DDR4_DQ6: U_D0.M7; also elsewhere on the board
DDR4_DQ7: U_D0.M8; also elsewhere on the board
DDR4_DQ8: U_D0.L1; also elsewhere on the board
DDR4_DQ9: U_D0.L2; also elsewhere on the board
DDR4_DQ10: U_D0.L3; also elsewhere on the board
DDR4_DQ11: U_D0.L4; also elsewhere on the board
DDR4_DQ12: U_D0.L5; also elsewhere on the board
DDR4_DQ13: U_D0.L6; also elsewhere on the board
DDR4_DQ14: U_D0.L7; also elsewhere on the board
DDR4_DQ15: U_D0.L8; also elsewhere on the board
DDR4_DQ16: U_D1.M1; also elsewhere on the board
DDR4_DQ17: U_D1.M2; also elsewhere on the board
DDR4_DQ18: U_D1.M3; also elsewhere on the board
DDR4_DQ19: U_D1.M4; also elsewhere on the board
DDR4_DQ20: U_D1.M5; also elsewhere on the board
DDR4_DQ21: U_D1.M6; also elsewhere on the board
DDR4_DQ22: U_D1.M7; also elsewhere on the board
DDR4_DQ23: U_D1.M8; also elsewhere on the board
DDR4_DQ24: U_D1.L1; also elsewhere on the board
DDR4_DQ25: U_D1.L2; also elsewhere on the board
DDR4_DQ26: U_D1.L3; also elsewhere on the board
DDR4_DQ27: U_D1.L4; also elsewhere on the board
DDR4_DQ28: U_D1.L5; also elsewhere on the board
DDR4_DQ29: U_D1.L6; also elsewhere on the board
DDR4_DQ30: U_D1.L7; also elsewhere on the board
DDR4_DQ31: U_D1.L8; also elsewhere on the board
DDR4_DQ32: U_D2.M1; also elsewhere on the board
DDR4_DQ33: U_D2.M2; also elsewhere on the board
DDR4_DQ34: U_D2.M3; also elsewhere on the board
DDR4_DQ35: U_D2.M4; also elsewhere on the board
DDR4_DQ36: U_D2.M5; also elsewhere on the board
DDR4_DQ37: U_D2.M6; also elsewhere on the board
DDR4_DQ38: U_D2.M7; also elsewhere on the board
DDR4_DQ39: U_D2.M8; also elsewhere on the board
DDR4_DQ40: U_D2.L1; also elsewhere on the board
DDR4_DQ41: U_D2.L2; also elsewhere on the board
DDR4_DQ42: U_D2.L3; also elsewhere on the board
DDR4_DQ43: U_D2.L4; also elsewhere on the board
DDR4_DQ44: U_D2.L5; also elsewhere on the board
DDR4_DQ45: U_D2.L6; also elsewhere on the board
DDR4_DQ46: U_D2.L7; also elsewhere on the board
DDR4_DQ47: U_D2.L8; also elsewhere on the board
DDR4_DQ48: U_D3.M1; also elsewhere on the board
DDR4_DQ49: U_D3.M2; also elsewhere on the board
DDR4_DQ50: U_D3.M3; also elsewhere on the board
DDR4_DQ51: U_D3.M4; also elsewhere on the board
DDR4_DQ52: U_D3.M5; also elsewhere on the board
DDR4_DQ53: U_D3.M6; also elsewhere on the board
DDR4_DQ54: U_D3.M7; also elsewhere on the board
DDR4_DQ55: U_D3.M8; also elsewhere on the board
DDR4_DQ56: U_D3.L1; also elsewhere on the board
DDR4_DQ57: U_D3.L2; also elsewhere on the board
DDR4_DQ58: U_D3.L3; also elsewhere on the board
DDR4_DQ59: U_D3.L4; also elsewhere on the board
DDR4_DQ60: U_D3.L5; also elsewhere on the board
DDR4_DQ61: U_D3.L6; also elsewhere on the board
DDR4_DQ62: U_D3.L7; also elsewhere on the board
DDR4_DQ63: U_D3.L8; also elsewhere on the board
DDR4_DQS0_N: U_D0.K2; also elsewhere on the board
DDR4_DQS0_P: U_D0.K1; also elsewhere on the board
DDR4_DQS1_N: U_D0.K4; also elsewhere on the board
DDR4_DQS1_P: U_D0.K3; also elsewhere on the board
DDR4_DQS2_N: U_D1.K2; also elsewhere on the board
DDR4_DQS2_P: U_D1.K1; also elsewhere on the board
DDR4_DQS3_N: U_D1.K4; also elsewhere on the board
DDR4_DQS3_P: U_D1.K3; also elsewhere on the board
DDR4_DQS4_N: U_D2.K2; also elsewhere on the board
DDR4_DQS4_P: U_D2.K1; also elsewhere on the board
DDR4_DQS5_N: U_D2.K4; also elsewhere on the board
DDR4_DQS5_P: U_D2.K3; also elsewhere on the board
DDR4_DQS6_N: U_D3.K2; also elsewhere on the board
DDR4_DQS6_P: U_D3.K1; also elsewhere on the board
DDR4_DQS7_N: U_D3.K4; also elsewhere on the board
DDR4_DQS7_P: U_D3.K3; also elsewhere on the board
GND: U_D0.A1, U_D0.A3, U_D0.A5, U_D0.A7, U_D0.B2, U_D0.B4, U_D0.B6, U_D0.B8, U_D0.C1, U_D0.C3, U_D0.C5, U_D0.C7, U_D0.D2, U_D0.D4, U_D0.D6, U_D0.D8, U_D0.E3, U_D0.E5, U_D0.E7, U_D1.A1, U_D1.A3, U_D1.A5, U_D1.A7, U_D1.B2, U_D1.B4, U_D1.B6, U_D1.B8, U_D1.C1, U_D1.C3, U_D1.C5, U_D1.C7, U_D1.D2, U_D1.D4, U_D1.D6, U_D1.D8, U_D1.E3, U_D1.E5, U_D1.E7, U_D2.A1, U_D2.A3, U_D2.A5, U_D2.A7, U_D2.B2, U_D2.B4, U_D2.B6, U_D2.B8, U_D2.C1, U_D2.C3, U_D2.C5, U_D2.C7, U_D2.D2, U_D2.D4, U_D2.D6, U_D2.D8, U_D2.E3, U_D2.E5, U_D2.E7, U_D3.A1, U_D3.A3, U_D3.A5, U_D3.A7, U_D3.B2, U_D3.B4, U_D3.B6, U_D3.B8, U_D3.C1, U_D3.C3, U_D3.C5, U_D3.C7, U_D3.D2, U_D3.D4, U_D3.D6, U_D3.D8, U_D3.E3, U_D3.E5, U_D3.E7; also elsewhere on the board
VDD_1V2: U_D0.A4, U_D0.A8, U_D0.B3, U_D0.B7, U_D0.C4, U_D0.C8, U_D0.D3, U_D0.D7, U_D0.E4, U_D0.E8, U_D1.A4, U_D1.A8, U_D1.B3, U_D1.B7, U_D1.C4, U_D1.C8, U_D1.D3, U_D1.D7, U_D1.E4, U_D1.E8, U_D2.A4, U_D2.A8, U_D2.B3, U_D2.B7, U_D2.C4, U_D2.C8, U_D2.D3, U_D2.D7, U_D2.E4, U_D2.E8, U_D3.A4, U_D3.A8, U_D3.B3, U_D3.B7, U_D3.C4, U_D3.C8, U_D3.D3, U_D3.D7, U_D3.E4, U_D3.E8; also elsewhere on the board
VPP_2V5: U_D0.A2, U_D0.A6, U_D0.B1, U_D0.B5, U_D0.C2, U_D0.C6, U_D0.D1, U_D0.D5, U_D0.E6, U_D1.A2, U_D1.A6, U_D1.B1, U_D1.B5, U_D1.C2, U_D1.C6, U_D1.D1, U_D1.D5, U_D1.E6, U_D2.A2, U_D2.A6, U_D2.B1, U_D2.B5, U_D2.C2, U_D2.C6, U_D2.D1, U_D2.D5, U_D2.E6, U_D3.A2, U_D3.A6, U_D3.B1, U_D3.B5, U_D3.C2, U_D3.C6, U_D3.D1, U_D3.D5, U_D3.E6; also elsewhere on the board
